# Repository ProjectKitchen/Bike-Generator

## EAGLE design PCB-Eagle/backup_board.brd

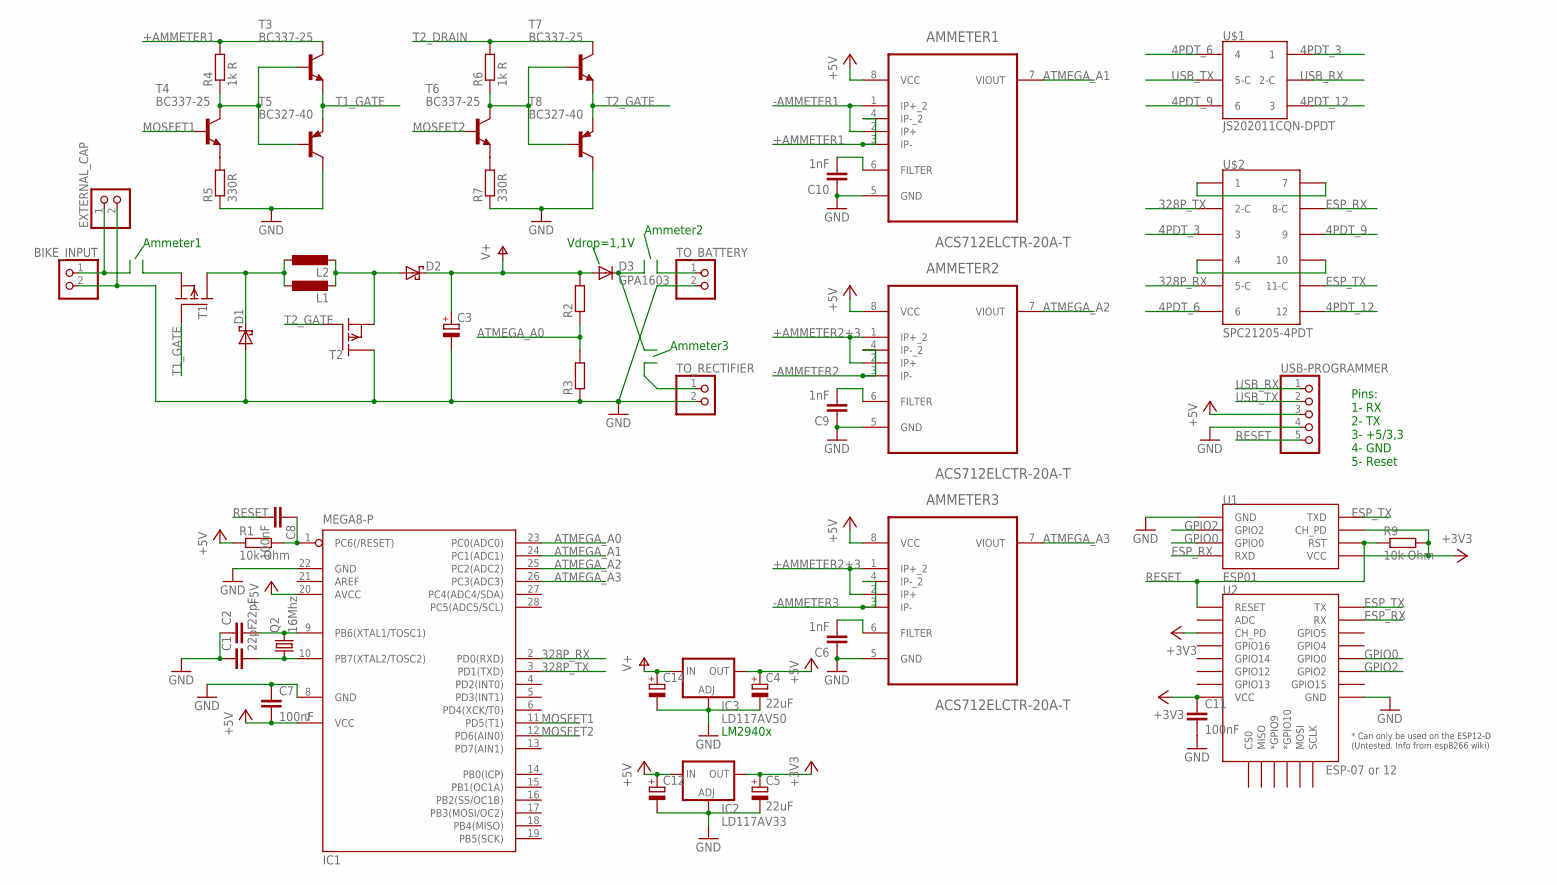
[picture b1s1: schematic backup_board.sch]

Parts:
AMMETER1, AMMETER2, AMMETER3: ACS712ELCTR-20A-T; SOIC127P600X175-8N
BIKE_INPUT: PINHD-1X2; 1X02
C1, C2: 22pF; C025-024X044
C3, C12, C14: CPOL-EUE3.5-8; E3,5-8
C4, C5: 22uF; E1,8-4
C6, C9, C10: 1nF; C025-024X044
C7, C11: 100nF; C025-024X044
C8: 100nF; C025-025X050
D1, D2: STPS1045; TO220AC
D3: GPA1603; C221B1A
EXTERNAL_CAP: PINHD-1X2; 1X02
IC1: MEGA8-P; DIL28-3
IC2: LD117AV33; TO220L1
IC3: LD117AV50; TO220L1
L1, L2: L-EUTJ4-U2; TJ4-U2
Q2: 16Mhz; HC49U70
R1, R9: 10k Ohm; 0204/7
R2, R3: R-EU_0207/10; 0207/10
R4, R6: 1k R; 0207/10
R5, R7: 330R; 0207/10
T1, T2: SUP65P06-20; TO220
T3, T4, T6, T7: BC337-25; TO92-CBE
T5, T8: BC327-40; TO92-EBC
TO_BATTERY: PINHD-1X2; 1X02
TO_RECTIFIER: PINHD-1X2; 1X02
U1: ESP01
U2: ESP-07 or 12; ESP12E-SMD
U$1: JS202011CQN-DPDT; 2X3_SWITCH
U$2: SPC21205-4PDT; 2X6_SWITCH
USB-PROGRAMMER: PINHD-1X5; 1X05

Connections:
4PDT_3: U$1.1, U$2.3
4PDT_6: U$1.4, U$2.6
4PDT_9: U$1.6, U$2.9
4PDT_12: U$1.3, U$2.12
328P_RX: IC1.2 (PD0(RXD)), U$2.5-C
328P_TX: IC1.3 (PD1(TXD)), U$2.2-C
+3V3: C5.+, C11.1, IC2.2 (OUT), R9.2, U1.CH_PD, U1.VCC, U2.CH_PD, U2.VCC
+5V: AMMETER1.8 (VCC), AMMETER2.8 (VCC), AMMETER3.8 (VCC), C4.+, C7.2, C12.+, IC1.7 (VCC), IC1.20 (AVCC), IC2.3 (IN), IC3.2 (OUT), R1.1, USB-PROGRAMMER.3
+AMMETER1: AMMETER1.3 (IP-), AMMETER1.4 (IP-_2), BIKE_INPUT.1, EXTERNAL_CAP.1, R4.2, T3.C
+AMMETER2+3: AMMETER2.1 (IP+_2), AMMETER2.2 (IP+), AMMETER3.1 (IP+_2), AMMETER3.2 (IP+), D3.C
-AMMETER1: AMMETER1.1 (IP+_2), AMMETER1.2 (IP+), T1.3 (S)
-AMMETER2: AMMETER2.3 (IP-), AMMETER2.4 (IP-_2), TO_BATTERY.1
-AMMETER3: AMMETER3.3 (IP-), AMMETER3.4 (IP-_2), TO_RECTIFIER.1
ATMEGA_A0: IC1.23 (PC0(ADC0)), R2.1, R3.2
ATMEGA_A1: AMMETER1.7 (VIOUT), IC1.24 (PC1(ADC1))
ATMEGA_A2: AMMETER2.7 (VIOUT), IC1.25 (PC2(ADC2))
ATMEGA_A3: AMMETER3.7 (VIOUT), IC1.26 (PC3(ADC3))
ESP_RX: U1.RX (RXD), U2.RXD0 (RX), U$2.8-C
ESP_TX: U1.TX (TXD), U2.TXD0 (TX), U$2.11-C
GND: AMMETER1.5 (GND), AMMETER2.5 (GND), AMMETER3.5 (GND), BIKE_INPUT.2, C1.1, C2.1, C3.-, C4.-, C5.-, C6.1, C7.1, C9.1, C10.1, C11.2, C12.-, C14.-, D1.A, EXTERNAL_CAP.2, IC1.8 (GND), IC1.22 (GND), IC2.1 (ADJ), IC3.1 (ADJ), R3.1, R5.1, R7.1, T2.2 (D), T5.C, T8.C, TO_BATTERY.2, TO_RECTIFIER.2, U1.GND, U2.GND, USB-PROGRAMMER.4
GPIO0: U1.GPIO0, U2.GPIO0
GPIO2: U1.GPIO2, U2.GPIO2
MOSFET1: IC1.11 (PD5(T1)), T4.B
MOSFET2: IC1.12 (PD6(AIN0)), T6.B
unnamed: C1.2, IC1.10 (PB7(XTAL2/TOSC2)), Q2.1
unnamed: C2.2, IC1.9 (PB6(XTAL1/TOSC1)), Q2.2
unnamed: U$2.4, U$2.10
unnamed: U$2.1, U$2.7
unnamed: C8.1, IC1.1 (PC6(/RESET)), R1.2
unnamed: R7.2, T6.E
unnamed: D1.C, L1.1, L2.1, T1.2 (D)
unnamed: R5.2, T4.E
unnamed: R6.1, T6.C, T7.B, T8.B
unnamed: R4.1, T3.B, T4.C, T5.B
unnamed: AMMETER3.6 (FILTER), C6.2
unnamed: AMMETER2.6 (FILTER), C9.2
unnamed: AMMETER1.6 (FILTER), C10.2
RESET: C8.2, R9.1, U1.RST, U2.RESET, USB-PROGRAMMER.5
T1_GATE: T1.1 (G), T3.E, T5.E
T2_DRAIN: D2.A, L1.2, L2.2, R6.2, T2.3 (S), T7.C
T2_GATE: T2.1 (G), T7.E, T8.E
USB_RX: U$1.2-C, USB-PROGRAMMER.1
USB_TX: U$1.5-C, USB-PROGRAMMER.2
V+: C3.+, C14.+, D2.C, D3.A, IC3.3 (IN), R2.2

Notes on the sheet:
Ammeter1
Ammeter2
Ammeter3
Vdrop=1,1V
LM2940x
Pins: 1- RX 2- TX 3- +5/3,3 4- GND 5- Reset

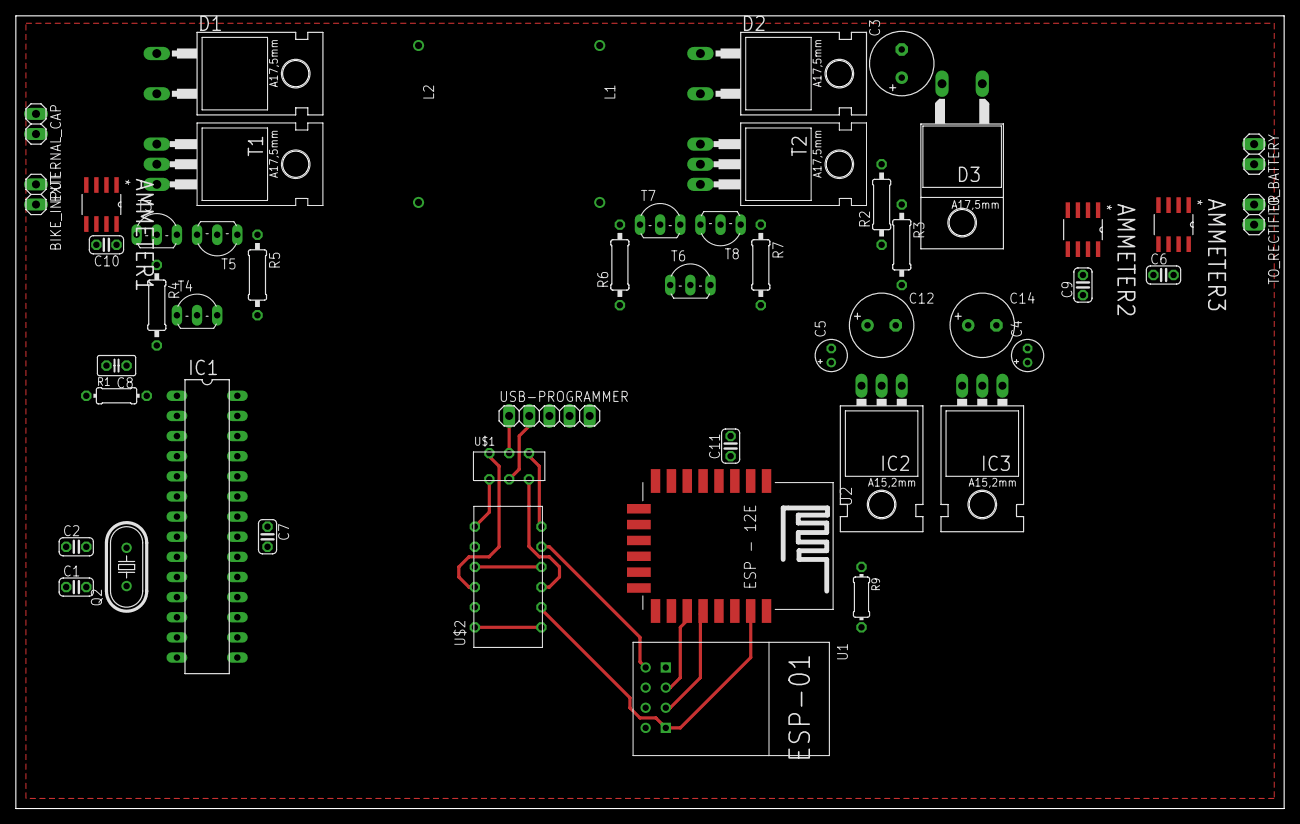
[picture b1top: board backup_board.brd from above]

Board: 2 copper layers, 160.0 x 100.0 mm, 50 parts (0 on the bottom side), 44 nets.

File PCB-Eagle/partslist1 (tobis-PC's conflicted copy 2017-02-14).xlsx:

Part | Value | Device | Package | Library | Price(1+) | Price(10+) | cheaper | link
AMMETER1 | ACS712ELCTR-20A-T | ACS712ELCTR-20A-T | SOIC127P600X175-8N | ACS712-20A_Farnell | 4.3099999999999996 | 2.48 | 2.48 | http://at.farnell.com/allegro-microsystems/acs712elctr-20a-t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
AMMETER2 | ACS712ELCTR-20A-T | ACS712ELCTR-20A-T | SOIC127P600X175-8N | ACS712-20A_Farnell | 4.3099999999999996 | 2.48 | 2.48 | http://at.farnell.com/allegro-microsystems/acs712elctr-20a-t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
AMMETER3 | ACS712ELCTR-20A-T | ACS712ELCTR-20A-T | SOIC127P600X175-8N | ACS712-20A_Farnell | 4.3099999999999996 | 2.48 | 2.48 | http://at.farnell.com/allegro-microsystems/acs712elctr-20a-t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
BIKE_INPUT |  | PINHD-1X2 | 1X02 | pinhead | 0.17 | 0.153 | 0.153 | http://at.farnell.com/camdenboss/ctbp3051-2/klemmenblock-wir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
C1 | 22pF | C-EU025-024X044 | C025-024X044 | rcl |  | 0.20599999999999999 | 0.20599999999999999 | http://at.farnell.com/vishay/k220j15c0gf53l2/kond-mlcc-c0g-n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
C2 | 22pF | C-EU025-024X044 | C025-024X044 | rcl |  | 0.20599999999999999 | 0.20599999999999999 | http://at.farnell.com/vishay/k220j15c0gf53l2/kond-mlcc-c0g-n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
C3 | 1000uF | CPOL-EUE5-10,5 | E5-10,5 | rcl |  | 0.60299999999999998 | 0.60299999999999998 | http://at.farnell.com/panasonic-electronic-components/eca-1e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
C4 | 22uF | CPOL-EUE2-5 | E2-5 | rcl | 4.99E-2 |  | 4.99E-2 | http://at.farnell.com/multicomp/mcgpr16v226m5x11/alu-elko-22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
C5 | 22uF | CPOL-EUE2-5 | E2-5 | rcl | 4.99E-2 |  | 4.99E-2 | http://at.farnell.com/multicomp/mcgpr16v226m5x11/alu-elko-22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
C6 | 1nF | C-EU025-024X044 | C025-024X044 | rcl |  | 3.7600000000000001E-2 | 3.7600000000000001E-2 | http://at.farnell.com/multicomp/mcbu5102k5/kondensator-mlcc-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
C7 | 100nF | C-EU025-024X044 | C025-024X044 | rcl |  | 7.3099999999999998E-2 | 7.3099999999999998E-2 | http://at.farnell.com/vishay/k104k15x7rf53l2/kondensator-mlc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
C8 | 100nF | C-EU025-025X050 | C025-025X050 | rcl |  | 7.3099999999999998E-2 | 7.3099999999999998E-2 | http://at.farnell.com/vishay/k104k15x7rf53l2/kondensator-mlc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
C9 | 1nF | C-EU025-024X044 | C025-024X044 | rcl |  | 3.7600000000000001E-2 | 3.7600000000000001E-2 | http://at.farnell.com/multicomp/mcbu5102k5/kondensator-mlcc-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
C10 | 1nF | C-EU025-024X044 | C025-024X044 | rcl |  | 3.7600000000000001E-2 | 3.7600000000000001E-2 | http://at.farnell.com/multicomp/mcbu5102k5/kondensator-mlcc-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
C11 | 100nF | C-EU025-024X044 | C025-024X044 | rcl |  | 7.3099999999999998E-2 | 7.3099999999999998E-2 | http://at.farnell.com/vishay/k104k15x7rf53l2/kondensator-mlc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
C12 | 22uF | CPOL-EUE2-5 | E2-5 | rcl | 4.99E-2 |  | 4.99E-2 | http://at.farnell.com/multicomp/mcgpr16v226m5x11/alu-elko-22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
C14 | 220uF | CPOL-EUE3.5-8 | E3,5-8 | rcl | 0.1193 |  | 0.1193 | http://at.farnell.com/multicomp/mcgpr25v227m8x11/alu-elko-22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
D1 |  | STPS1045 | TO220AC | stps1045_own | 0.77400000000000002 |  | 0.77400000000000002 | http://at.farnell.com/stmicroelectronics/stps1045d/schottky-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
D2 |  | STPS1045 | TO220AC | stps1045_own | 0.77400000000000002 |  | 0.77400000000000002 | http://at.farnell.com/stmicroelectronics/stps1045d/schottky-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
D3 | GPA1603 | DIODE-C221B1A | C221B1A | diode | ??? |  | ???
EXTERNAL_CAP |  | PINHD-1X2 | 1X02 | pinhead | 0.17 | 0.153 | 0.153 | http://at.farnell.com/camdenboss/ctbp3051-2/klemmenblock-wir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
IC1 | MEGA8-P | MEGA8-P | DIL28-3 | atmel | 3.33 |  | 3.33 | http://at.farnell.com/atmel/atmega328p-pu/mcu-8bit-avr-32k-f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
IC2 | LD117AV33 | LD117AV33 | TO220L1 | v-reg | 0.39700000000000002 |  | 0.39700000000000002 | http://at.farnell.com/stmicroelectronics/ld1117v33c/spannung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
IC3 | LD117AV50 | LD117AV50 | TO220L1 | v-reg | 0.624 |  | 0.624 | http://at.farnell.com/stmicroelectronics/ld1117v50/v-reg-ldo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
L1 |  | L-EUTJ4-U2 | TJ4-U2 | rcl | 5.22 |  | 5.22 | http://at.farnell.com/coilcraft/pcv-2-104-10l/leistungsinduk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
L2 |  | L-EUTJ4-U2 | TJ4-U2 | rcl | 5.22 |  | 5.22 | or | http://at.farnell.com/coilcraft/pcv-2-184-10l/leistungsinduk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
Q2 | 16Mhz | CRYSTALHC49U70 | HC49U70 | crystal | 0.182 |  | 0.182 | http://at.farnell.com/qantek-technology-corporation/qcl16-00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
R1 | 10k Ohm | R-EU_0207/10 | 0207/10 | resistor |  | 3.1699999999999999E-2 | 3.1699999999999999E-2 | http://at.farnell.com/te-connectivity/cfr25j10k/kohleschicht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
R2 | 1kR | R-EU_0207/10 | 0207/10 | resistor |  | 4.9200000000000001E-2 | 4.9200000000000001E-2 | http://at.farnell.com/te-connectivity/lr1f1k0/metallschichtw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
R3 | 390R | R-EU_0207/10 | 0207/10 | resistor |  | 5.5399999999999998E-2 | 5.5399999999999998E-2 | http://at.farnell.com/multicomp/mcmf006ff3900a50/metallschic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
R4 | 1k R | R-EU_0207/10 | 0207/10 | resistor |  | 4.9200000000000001E-2 | 4.9200000000000001E-2 | http://at.farnell.com/te-connectivity/lr1f1k0/metallschichtw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
R5 | 390R | R-EU_0207/10 | 0207/10 | resistor |  | 5.5399999999999998E-2 | 5.5399999999999998E-2 | http://at.farnell.com/multicomp/mcmf006ff3900a50/metallschic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
R6 | 1k R | R-EU_0207/10 | 0207/10 | resistor |  | 4.9200000000000001E-2 | 4.9200000000000001E-2 | http://at.farnell.com/te-connectivity/lr1f1k0/metallschichtw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
R7 | 390R | R-EU_0207/10 | 0207/10 | resistor |  | 5.5399999999999998E-2 | 5.5399999999999998E-2 | http://at.farnell.com/multicomp/mcmf006ff3900a50/metallschic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
R9 | 10k Ohm | R-EU_0207/10 | 0207/10 | resistor |  | 3.1699999999999999E-2 | 3.1699999999999999E-2 | http://at.farnell.com/te-connectivity/cfr25j10k/kohleschicht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
T1 | SUP65P06-20 | SUP65P06-20 | TO220 | transistor-fet | 1.1299999999999999 |  | 1.1299999999999999 | http://at.farnell.com/fairchild-semiconductor/fqp27p06/mosfe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
T2 | SUP65P06-20 | SUP65P06-20 | TO220 | transistor-fet | 1.1299999999999999 |  | 1.1299999999999999 | http://at.farnell.com/fairchild-semiconductor/fqp27p06/mosfe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
T3 | BC33725BU | BC337-25-NPN-TO92-CBE | TO92-CBE | transistor |  | 0.17299999999999999 | 0.17299999999999999 | http://at.farnell.com/fairchild-semiconductor/bc33725bu/tran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
T4 | BC33725BU | BC337-25-NPN-TO92-CBE | TO92-CBE | transistor |  | 0.17299999999999999 | 0.17299999999999999 | http://at.farnell.com/fairchild-semiconductor/bc33725bu/tran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
T5 | BC32740TA | BC327-40 | TO92-EBC | transistor-pnp |  | 7.6999999999999999E-2 | 7.6999999999999999E-2 | http://at.farnell.com/fairchild-semiconductor/bc32740ta/tran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
T6 | BC33725BU | BC337-25-NPN-TO92-CBE | TO92-CBE | transistor |  | 0.17299999999999999 | 0.17299999999999999 | http://at.farnell.com/fairchild-semiconductor/bc33725bu/tran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
T7 | BC33725BU | BC337-25-NPN-TO92-CBE | TO92-CBE | transistor |  | 0.17299999999999999 | 0.17299999999999999 | http://at.farnell.com/fairchild-semiconductor/bc33725bu/tran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
T8 | BC32740TA | BC327-40 | TO92-EBC | transistor-pnp |  | 7.6999999999999999E-2 | 7.6999999999999999E-2 | http://at.farnell.com/fairchild-semiconductor/bc32740ta/tran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
TO_BATTERY |  | PINHD-1X2 | 1X02 | pinhead | 0.17 | 0.153 | 0.153 | http://at.farnell.com/camdenboss/ctbp3051-2/klemmenblock-wir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
TO_RECTIFIER |  | PINHD-1X2 | 1X02 | pinhead | 0.17 | 0.153 | 0.153 | http://at.farnell.com/camdenboss/ctbp3051-2/klemmenblock-wir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
U$1 | JS202011CQN-DPDT | JS202011CQN-DPDT | 2X3_SWITCH | Library_TW | 0.39400000000000002 |  | 0.39400000000000002 | http://at.farnell.com/c-k-components/js202011cqn/schalter-dp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
U$2 | SPC21205-4PDT | SPC21205-4PDT | 2X6_SWITCH | Library_TW | 1.78 |  | 1.78 | http://at.farnell.com/multicomp/spc21205/schiebeschalter-4pd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
U1 | ESP01 | ESP01 | ESP01 | esp8266modules | 6.49 |  | 6.49 | http://www.digikey.at/product-detail/en/sparkfun-electronics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
U2 | ESP-07 or 12 | ESP12ESMD | ESP12E-SMD | esp8266modules |  |  | 0
USB-PROGRAMMER |  | PINHD-1X5 | 1X05 | pinhead | 0.128 |  | 0.128 | http://at.farnell.com/molex/22-23-2051/stecker-pin-5kont/dp/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
PCB-RAW_MATERIAL |  |  |  |  |  |  | 7.58 | http://at.farnell.com/kelan/141301/leiterplatte-fotopositivl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
 |  |  |  |  |  | Total: | 46.044299999999978

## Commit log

2017-12-04 Uploaded Bachelor paper and Guides
2017-12-04 Added PCB files and Software
2018-01-03 added fotos & bom
